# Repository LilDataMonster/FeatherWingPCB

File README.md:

The `FeatherWing_KC5` directory of this repository contains a
[KiCad][1] 5 [template][4] for making [FeatherWing][2] boards.

Since Adafruit does not provide standardized names for the GPIO pins,
I found these online.

The PCB has been printed and fits with Feathers.

## License

This repository is licensed under [the same terms as the KiCad
libraries][9], which is the [CC-BY-SA 4.0][10] license, with an
exception that says that electronic designs based on this repository
are not bound by the attribution and share-alike conditions.

[1]: http://kicad-pcb.org/
[2]: https://learn.adafruit.com/adafruit-feather/feather-specification
[3]: https://funwithsoftware.org/posts/2018-08-31-feather-ascii-art-pinout.html
[4]: http://docs.kicad-pcb.org/5.1.2/en/kicad/kicad.html#project_templates
[9]: https://forum.kicad.info/t/kicad-library-licensing/7856
[10]: https://creativecommons.org/licenses/by-sa/4.0/legalcode
# FeatherWingPCB

Allows up to 10 DS18B20 temperature sensors to be connected to a Feather via A0.

Assumes use of 2.54mm terminal blocks as well as a 4.7k resistor

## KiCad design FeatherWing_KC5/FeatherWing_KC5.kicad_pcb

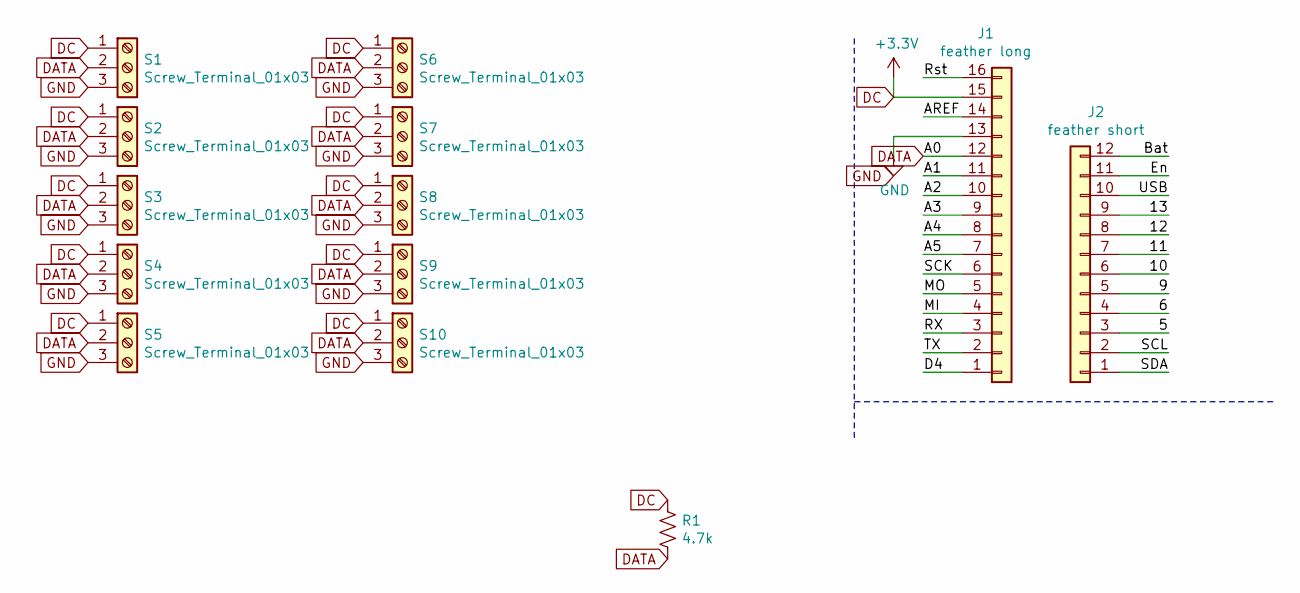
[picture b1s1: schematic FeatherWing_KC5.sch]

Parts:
J1: feather long; PinHeader_1x16_P2.54mm_Vertical
J2: feather short; PinHeader_1x12_P2.54mm_Vertical
R1: 4.7k; R_Axial_DIN0207_L6.3mm_D2.5mm_P7.62mm_Horizontal
S1, S2, S3, S4, S5, S6, S7, S8, S9, S10: Screw_Terminal_01x03; TerminalBlock_TE_282834-3_1x03_P2.54mm_Horizontal

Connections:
/5: J2.3
/6: J2.4
/9: J2.5
/10: J2.6
/11: J2.7
/12: J2.8
/13: J2.9
/A1: J1.11
/A2: J1.10
/A3: J1.9
/A4: J1.8
/A5: J1.7
/AREF: J1.14
/Bat: J2.12
/D4: J1.1
/En: J2.11
/MI: J1.4
/MO: J1.5
/RX: J1.3
/Rst: J1.16
/SCK: J1.6
/SCL: J2.2
/SDA: J2.1
/TX: J1.2
/USB: J2.10
DATA: J1.12, R1.2, S1.2, S2.2, S3.2, S4.2, S5.2, S6.2, S7.2, S8.2, S9.2, S10.2
DC: J1.15, R1.1, S1.1, S2.1, S3.1, S4.1, S5.1, S6.1, S7.1, S8.1, S9.1, S10.1
GND: J1.13, S1.3, S2.3, S3.3, S4.3, S5.3, S6.3, S7.3, S8.3, S9.3, S10.3

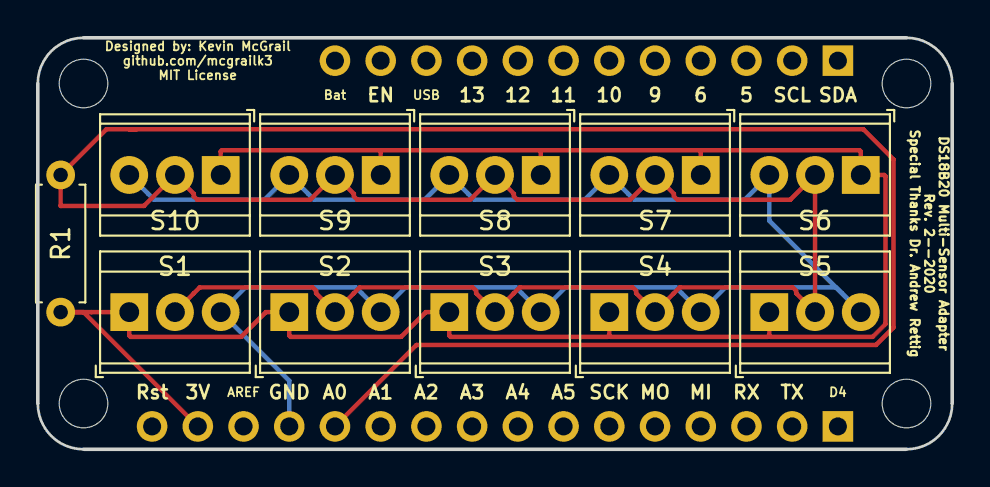
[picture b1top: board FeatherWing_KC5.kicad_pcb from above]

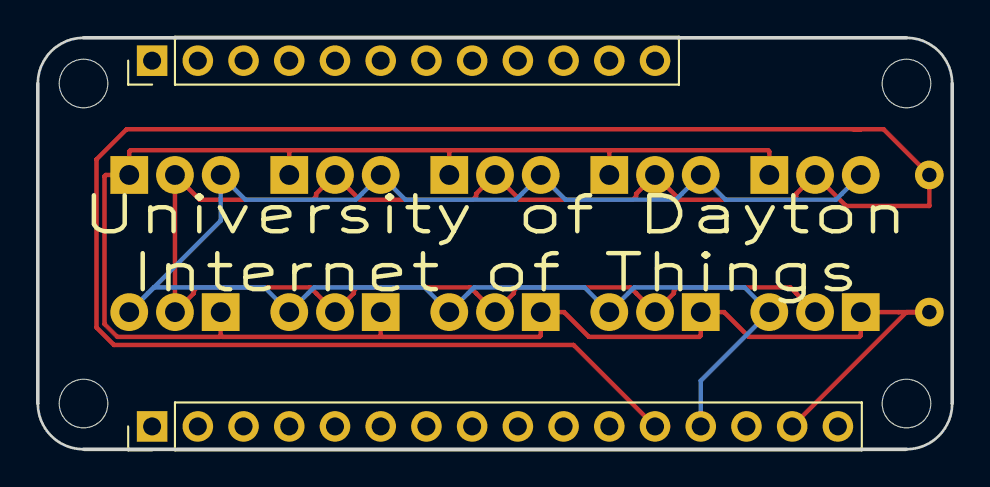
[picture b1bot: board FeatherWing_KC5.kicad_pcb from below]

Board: 2 copper layers, 50.8 x 22.9 mm, 13 parts (2 on the bottom side), 3 nets.

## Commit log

2019-11-26 Initial
2020-02-13 being printed

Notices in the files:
FeatherWing_KC5/FeatherWing_KC5.kicad_pcb:
MIT License
